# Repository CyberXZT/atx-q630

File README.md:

# ATX - Quadra 630 PSU Conversion Kit

This is an ATX/Quadra 630 PSU conversion PCB that I designed a while ago and
never got around to uploading.

[BOM](bom.csv)

**I am not an electrical engineer. I take no responsibility for any damage
these designs may cause. Use these designs with extreme caution.**

## Quick Notes
* R2 is unused.
* U1, C1, and C2 provide the -12V rail. If your PSU provides -12V, do not
populate these. Instead, bridge the "ATX -12V" jumper.
* 3.3V is not connected by default. The PSU in the original Quadra 630 PSU
uses this wire for ground. While the motherboards I tested did not actually
connect this wire, I have left it not connected by default. If you need 3.3V,
bridge the "ATX 3V3" jumper.
* I can't a good connector for the 6-pin "MAC-AUX" connector. The BOM
references the best fitting part although the smaller wall has to be cut in
order for the connector to fit. 
* PCB was designed with 2oz copper in mind.

## License and Copyright

Copyright &copy; Dean Winger 2021

This work is licensed under the Creative Commons
Attribution-ShareAlike 4.0 International License. To view a copy of
this license, visit http://creativecommons.org/licenses/by-sa/4.0/ or
send a letter to Creative Commons, PO Box 1866, Mountain View, CA
94042, USA.

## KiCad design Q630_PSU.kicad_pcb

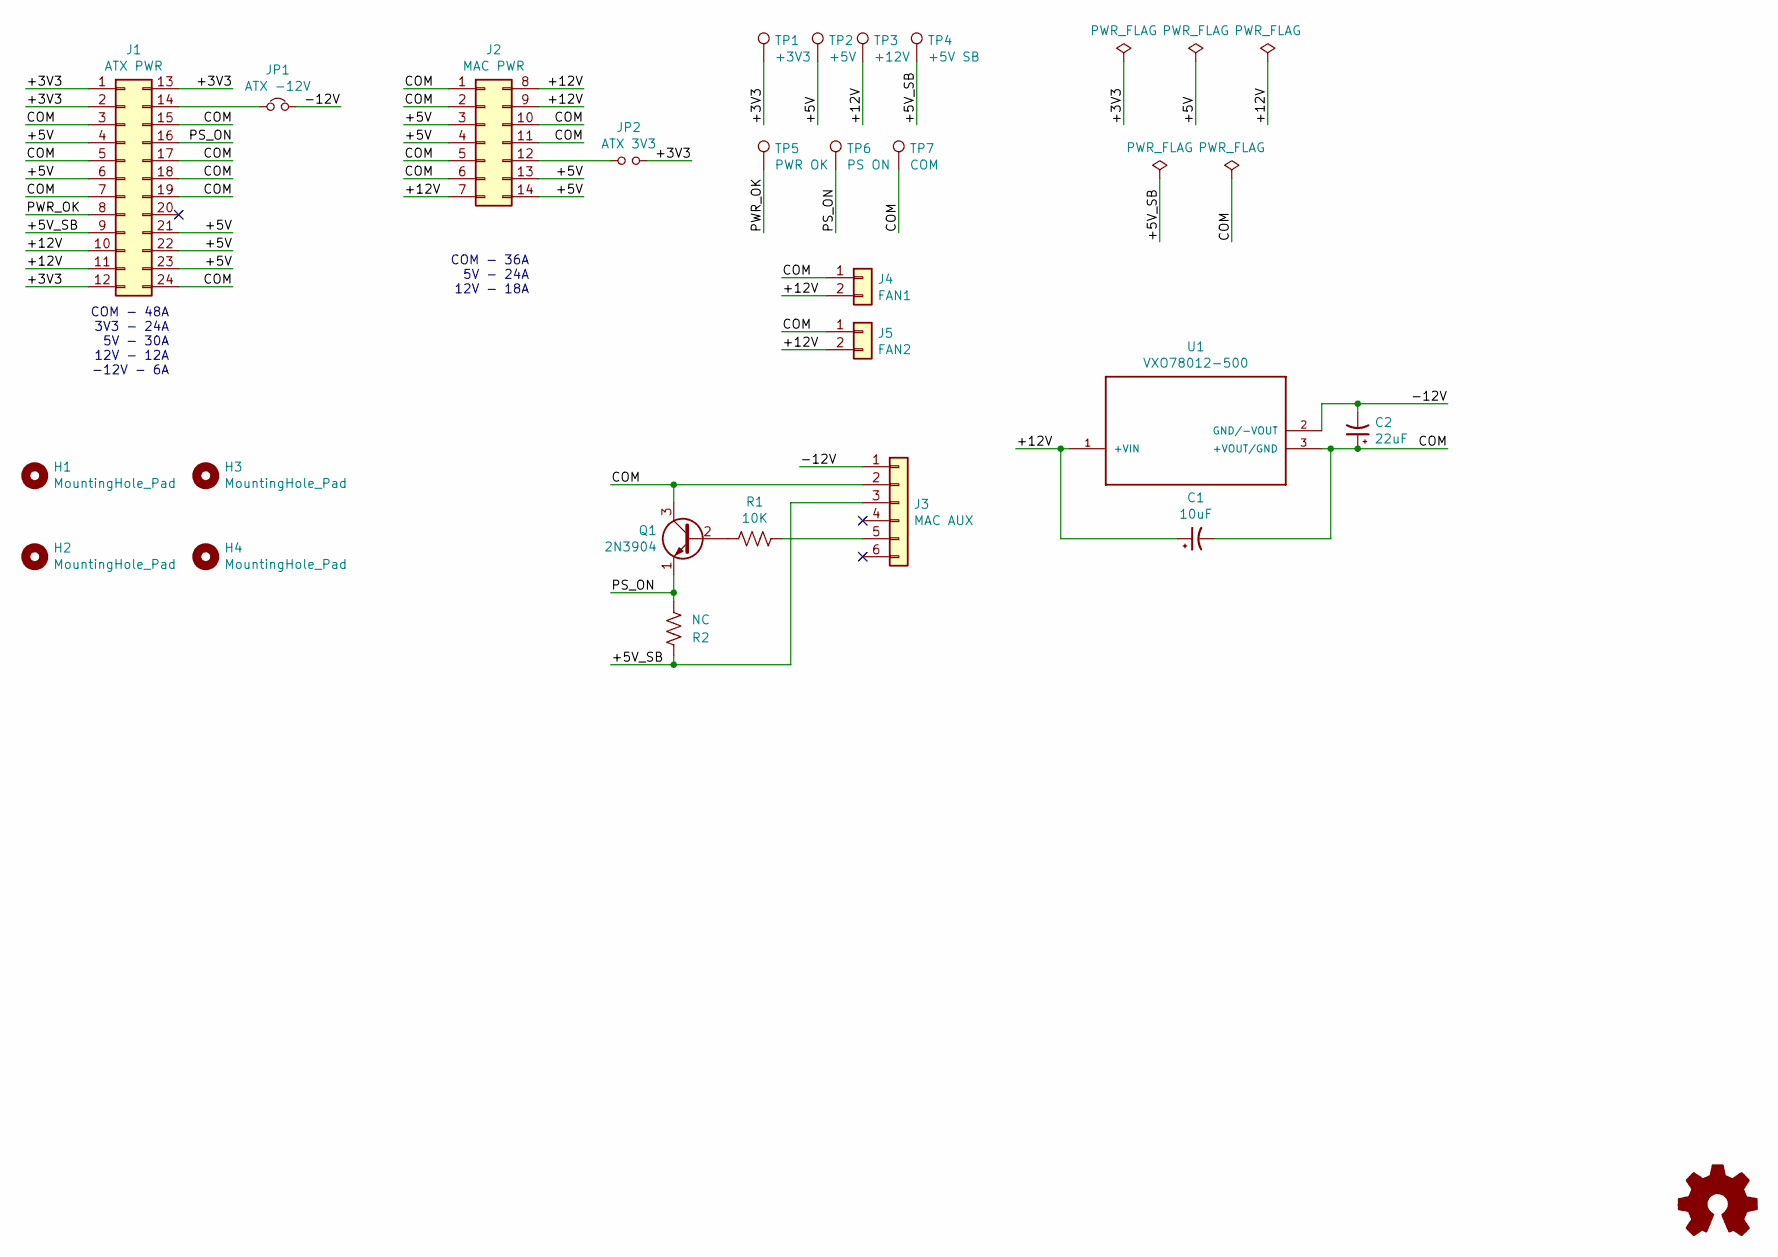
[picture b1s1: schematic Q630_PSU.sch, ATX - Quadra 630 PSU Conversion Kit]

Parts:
C1: 10uF; C1
C2: 22uF; C2
H1, H2, H3, H4: MountingHole_Pad; MountingHole_3.2mm_M3_Pad
J1: ATX PWR; Molex_Mini-Fit_Jr_5566-24A2_2x12_P4.20mm_Vertical
J2: MAC PWR; Molex_Mini-Fit_Jr_5566-14A2_2x07_P4.20mm_Vertical
J3: MAC AUX; PinSocket_1x06_P2.54mm_Vertical
J4: FAN1; PinSocket_1x02_P2.54mm_Vertical
J5: FAN2; PinSocket_1x02_P2.54mm_Vertical
JP1: ATX -12V; SolderJumper-2_P1.3mm_Open_Pad1.0x1.5mm
JP2: ATX 3V3; J2
Q1: 2N3904; TO-92_Inline_Wide
R1: 10K; R_Axial_DIN0411_L9.9mm_D3.6mm_P12.70mm_Horizontal
R2: NC; R_Axial_DIN0411_L9.9mm_D3.6mm_P12.70mm_Horizontal
TP1: +3V3; TestPoint_Pad_D1.0mm
TP2: +5V; TestPoint_Pad_D1.0mm
TP3: +12V; TestPoint_Pad_D1.0mm
TP4: +5V SB; TestPoint_Pad_D1.0mm
TP5: PWR OK; TestPoint_Pad_D1.0mm
TP6: PS ON; TestPoint_Pad_D1.0mm
TP7: COM; TestPoint_Pad_D1.0mm
U1: VXO78012-500; CONV_VXO78012-500

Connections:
/+3V3: J1.1, J1.2, J1.12, J1.13, JP2.2, TP1.1
/+5V: J1.4, J1.6, J1.21, J1.22, J1.23, J2.3, J2.4, J2.13, J2.14, TP2.1
/+5V_SB: J1.9, J3.3, R2.1, TP4.1
/+12V: C1.1, J1.10, J1.11, J2.7, J2.8, J2.9, J4.2, J5.2, TP3.1, U1.1 (+VIN)
/-12V: C2.2, J3.1, JP1.2, U1.2 (GND/-VOUT)
/COM: C1.2, C2.1, J1.3, J1.5, J1.7, J1.15, J1.17, J1.18, J1.19, J1.24, J2.1, J2.2, J2.5, J2.6, J2.10, J2.11, J3.2, J4.1, J5.1, Q1.3 (C), TP7.1, U1.3 (+VOUT/GND)
/PS_ON: J1.16, Q1.1 (E), R2.2, TP6.1
/PWR_OK: J1.8, TP5.1
unnamed: J1.14, JP1.1
unnamed: J2.12, JP2.1
unnamed: J3.5, R1.1
unnamed: Q1.2 (B), R1.2

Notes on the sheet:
COM - 48A 3V3 - 24A 5V - 30A 12V - 12A -12V - 6A
COM - 36A 5V - 24A 12V - 18A

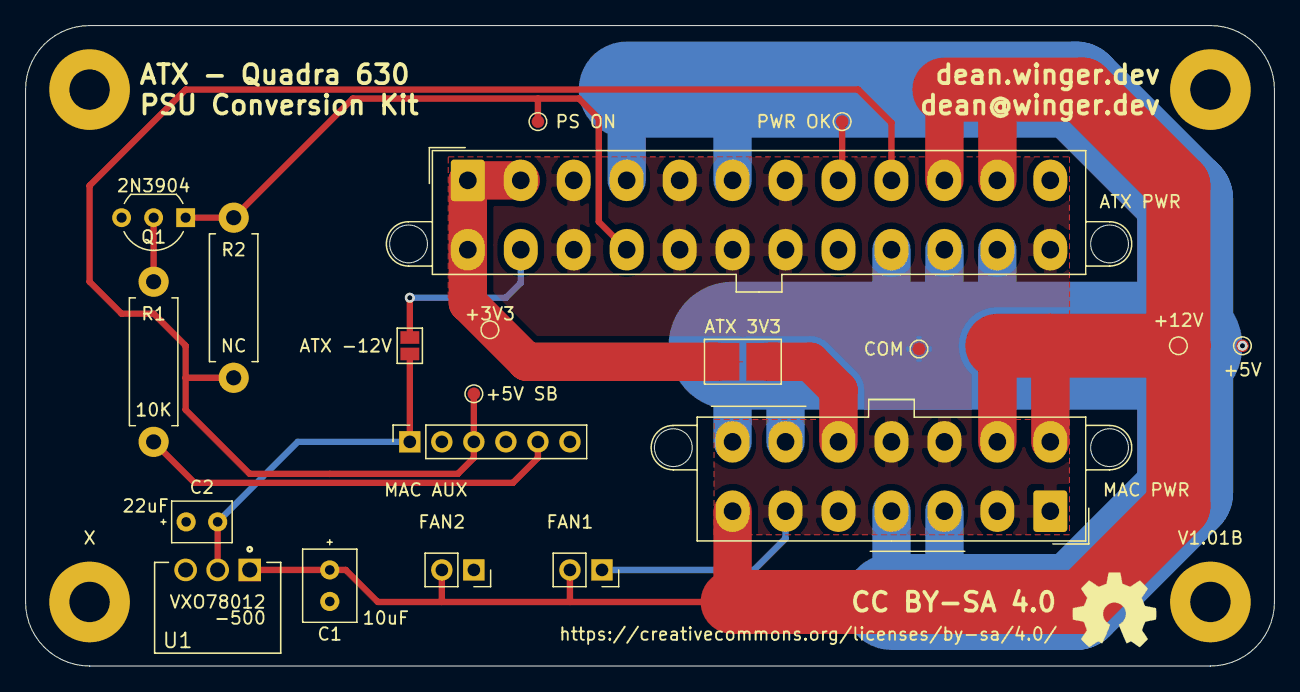
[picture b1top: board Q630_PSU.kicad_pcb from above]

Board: 2 copper layers, 99.1 x 50.8 mm, 24 parts (0 on the bottom side), 12 nets.

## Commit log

2021-02-16 Updated README.md with additional notes.
2021-02-16 Screenshot and further README.md updates.
2021-03-06 Removed unused component from BOM.

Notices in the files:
Q630_PSU.kicad_pcb:
CC BY-SA 4.0
https://creativecommons.org/licenses/by-sa/4.0
